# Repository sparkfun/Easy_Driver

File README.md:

Easy Driver
===========

[*Easy Driver (ROB-12779)*](https://www.sparkfun.com/products/12779)

The EasyDriver is a simple to use stepper motor driver, compatible with anything that can output a digital 0 to 5V pulse (or 0 to 3.3V pulse if you solder SJ2 closed on the EasyDriver). 
The EasyDriver requires a 7V to 20V supply to power the motor and can power any voltage of stepper motor.

Repository Contents
-------------------
* **/Firmware** - Any firmware that the part ships with, 
* **/Hardware** - All Eagle design files (.brd, .sch, .STL)
* **/Production** - Test bed files and production panel files

Documentation
--------------

* **[Hookup Guide](https://learn.sparkfun.com/tutorials/easy-driver-hook-up-guide)** - Basic hookup guide for the Easy Driver.
* **[Brian Schmalz: Easy Driver](http://schmalzhaus.com/EasyDriver/)** - More specs and FAQ.

License Information
-------------------

_Note: This product is a collaboration with Brian Schmalz. A portion of each sales goes back to him for product support and continued development._

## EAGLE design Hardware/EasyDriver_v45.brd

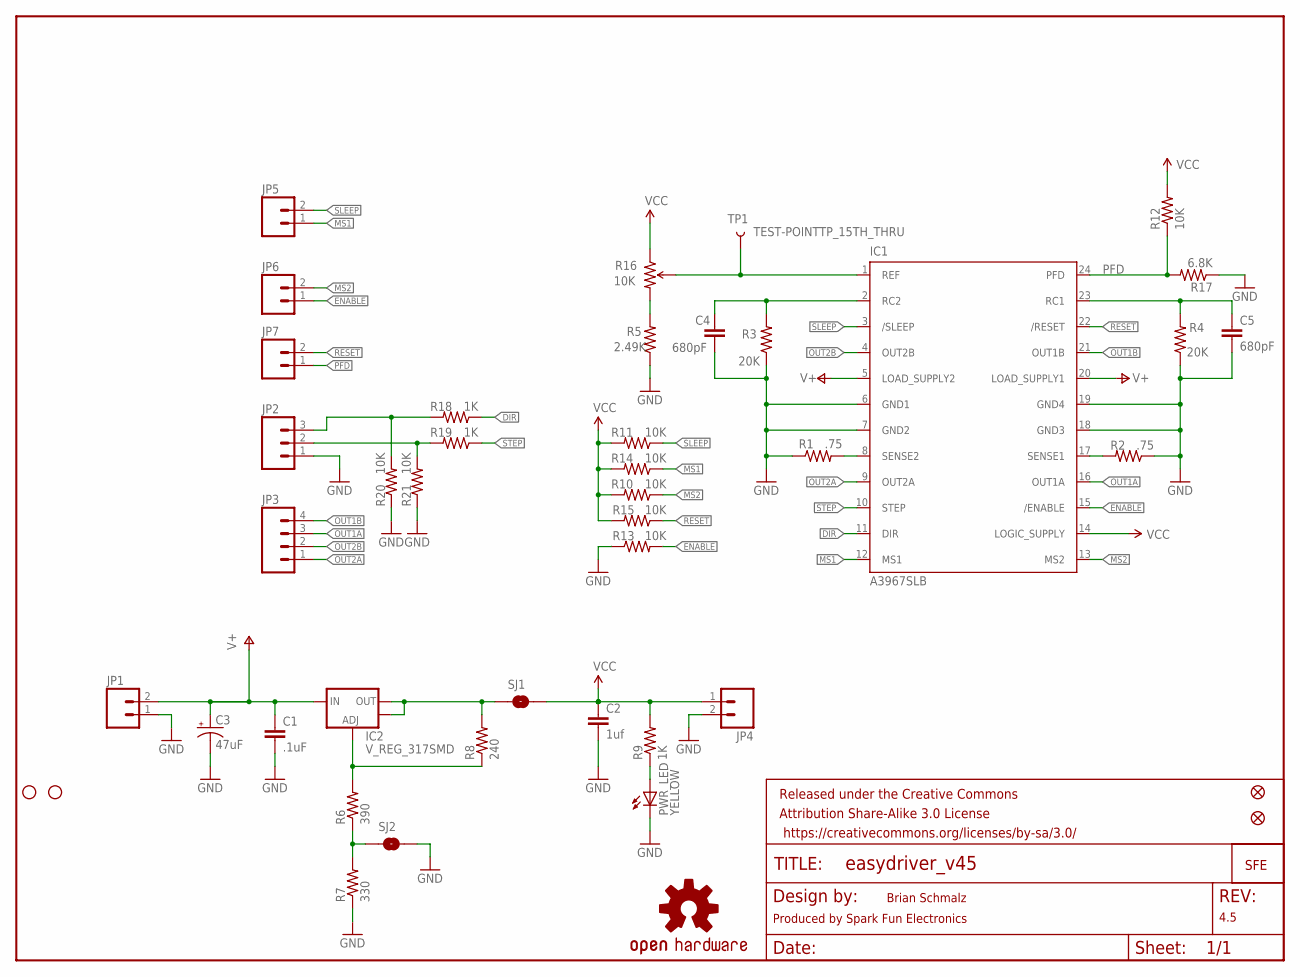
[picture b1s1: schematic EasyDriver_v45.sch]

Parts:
C1: .1uF; 0603-CAP
C2: 1uf; 0603-CAP
C3: 47uF; PANASONIC_D
C4, C5: 680pF; 0603-CAP
FID1, FID2: FIDUCIAL1X2; FIDUCIAL-1X2
FRAME2: FRAME-LETTER; CREATIVE_COMMONS
IC1: A3967SLB; SO24W
IC2: V_REG_317SMD; SOT223
JP1, JP4, JP5, JP6, JP7: M021X02_NO_SILK; 1X02_NO_SILK
JP2: M031X03_NO_SILK; 1X03_NO_SILK
JP3: M041X04_NO_SILK; 1X04_NO_SILK
JP8, JP9: STAND-OFF
LOGO1: OSHW-LOGOS; OSHW-LOGO-S
PWR_LED: YELLOW; LED-0603
R1, R2: .75; 0805
R3, R4: 20K; 0603-RES
R5: 2.49K; 0603-RES
R6: 390; 0603-RES
R7: 330; 0603-RES
R8: 240; 0603-RES
R9, R18, R19: 1K; 0603-RES
R10, R11, R12, R13, R14, R15, R20, R21: 10K; 0603-RES
R16: 10K; TRIMPOT-3MM-2
R17: 6.8K; 0603-RES
SJ1: SOLDERJUMPERTRACE; SJ_2S-TRACE
SJ2: SOLDERJUMPERNO; SJ_2S-NO
TP1: TEST-POINTTP_15TH_THRU; TP_15TH
U$2: LOGO-SFENEW; SFE-NEW-WEBLOGO

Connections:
5V_ALT: IC2.2 (OUT), IC2.4 (OUT), R8.2, SJ1.1
DIR: IC1.11 (DIR), R18.1
DIR_IN: JP2.3, R18.2, R20.2
ENABLE: IC1.15 (/ENABLE), JP6.1, R13.2
GND: C1.2, C2.2, C3.-, C4.2, C5.2, IC1.6 (GND1), IC1.7 (GND2), IC1.18 (GND3), IC1.19 (GND4), JP1.1, JP2.1, JP4.2, PWR_LED.C, R1.1, R2.1, R3.1, R4.1, R5.1, R7.1, R13.1, R17.1, R20.1, R21.1, SJ2.2
MS1: IC1.12 (MS1), JP5.1, R14.1
MS2: IC1.13 (MS2), JP6.2, R10.1
unnamed: IC1.8 (SENSE2), R1.2
unnamed: PWR_LED.A, R9.1
unnamed: IC1.17 (SENSE1), R2.2
unnamed: R6.1, R7.2, SJ2.1
unnamed: C4.1, IC1.2 (RC2), R3.2
unnamed: IC2.1 (ADJ), R6.2, R8.1
unnamed: C5.1, IC1.23 (RC1), R4.2
unnamed: R5.2, R16.3 (CW)
OUT1A: IC1.16 (OUT1A), JP3.3
OUT1B: IC1.21 (OUT1B), JP3.4
OUT2A: IC1.9 (OUT2A), JP3.1
OUT2B: IC1.4 (OUT2B), JP3.2
PFD: IC1.24 (PFD), JP7.1, R12.1, R17.2
RESET: IC1.22 (/RESET), JP7.2, R15.1
SLEEP: IC1.3 (/SLEEP), JP5.2, R11.1
STEP: IC1.10 (STEP), R19.1
STEP_IN: JP2.2, R19.2, R21.2
V+: C1.1, C3.+, IC1.5 (LOAD_SUPPLY2), IC1.20 (LOAD_SUPPLY1), IC2.3 (IN), JP1.2
VCC: C2.1, IC1.14 (LOGIC_SUPPLY), JP4.1, R9.2, R10.2, R11.2, R12.2, R14.2, R15.2, R16.1 (CCW), SJ1.2
VREF: IC1.1 (REF), R16.2 (WIPER), TP1.P$1

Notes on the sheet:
Brian Schmalz
Produced by Spark Fun Electronics
4.5

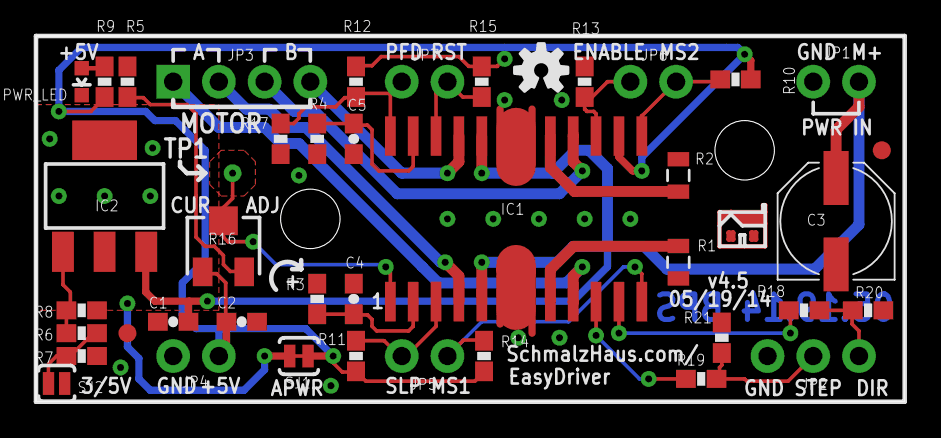
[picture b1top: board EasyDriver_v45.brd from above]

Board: 2 copper layers, 48.3 x 20.3 mm, 47 parts (1 on the bottom side), 27 nets.

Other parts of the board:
U$1: SCHMALZHAUS_SMALL

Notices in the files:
EasyDriver_v45/EasyDriver_v45.sch:
licensed under a Creative Commons
Attribution Share Alike (CC BY-SA) 3.0 US License
Copyright 2010-2014
Swithed from CC BY 3.0 to CC BY-SA 3.0 license
parts and their libraries:
SparkFun-Resistors: Licensing: Creative Commons ShareAlike 4.0 International - https://creativecommons.org/licenses/by-sa/4.0
SparkFun-Aesthetics: Released under the Creative Commons Attribution Share-Alike 4.0 License
SparkFun-Aesthetics: https://creativecommons.org/licenses/by-sa/4.0
